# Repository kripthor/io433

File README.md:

# Project IO433

```
 ___ ___  _ _ ________
|_ _/ _ \| | |__ /__ /
 | | (_) |_  _|_ \|_ \
|___\___/  |_|___/___/
                       
```
##
This is a fork (v0.21) for my personal use of the original io433 project by Krypthor.
Added "Jam" capability. This is really fun, no on in vincity can use 433Mhz devices :))

## Description

IO433 is an open-source ESP32 (TTGO T-Display) & CC1101 based 433Mhz sniffer. It is currently work in progress.
It can sniff, store, replay, dump and monitor most 433Mhz (currently ASK-OOK only) signals.
These include garage door openers, remote doorbells, sensors and similar devices.

The core of this project aims to be its simplicity, reliability and versatility.
With a couple of ICs and a by 'connecting some wires', or soldering a breakout board, one can start messing around with 433Mhz devices and decode their communications protocols.
It's mainly a proof-of-concept but already encompasses several very useful features.

```bash
│  # The current dir is a platformIO project and can be imported straight from here.
├── arduino  # an example arduino project that implements a remote for some ASK-OOK-PWM signals based on a FS1000A
├── docs     # docs and pictures
├── include  # project helper files 
├── lib    #some needed libraries with specific modifications for this project
├── libsigrokdecode   # a modified PWM decoder that shows bits and nibbles (sigrok/PulseView)
└── src # project main files
```

## Bill of Materials

| Qty. | Description | Obs. |
|------|------------------------|-----------------------------------------------------------------|
| 1 | ESP32 TTGO T-Display | ESP32 controller with a 1.14" LCD and two buttons for navigation |
| 1 | TI-CC1101 or E07-M1101D | CC1101 based modules for 433Mhz (and other frequencies) communications |
| 1 | io433 PCB| Order a PCB or etch one or just grab some wires :) |
| 1 | Battery | Optional 3.7v battery

* All the components can be easily found in the usual online stores such as *AliExpress* ([ESP32 TTGO T-Display](https://aliexpress.com/wholesale?SearchText=ttgo+t+display+esp32)) - [CC1101](https://aliexpress.com/wholesale?SearchText=cc1101)), *Amazon*, *eBay*, etc.
* The breakout pcb and schematics files are under the docs/ directory: 
[IO433 Schematic](docs/breakout.sch)
[IO433 Board](docs/breakout.brd)

## IO433 Wiring

### Prototype photo and assembly suggestion

This is just a suggestion on how to wire the ESP32 and the CC1101. A perforated PCB can be used to make the prototype more sturdy. Or you can just order a pre-fabricated board, like the one bellow:

### IO433 Wiring

Details of the wiring between the ESP32 and TI-CC1101 (above) and the E07-M1101D (below). The pinout choosing is important. If changed, not only the code should change to reflect the new pinout, as one must make sure the corresponding ports on the ESP32 support the I/O operation mode that the code needs. 
* **Important note**: the green wire connects to IO2 on the ESP32, regardless of what you see in some pictures.
* **Important note 2**: You need to change the file ./include/CC1101utils.h to reflect which CC1101 model you are using.

### IO433 PCB Schematics
docs/breakout.sch

docs/breakout.brd

### Assembly with PCB

Solder the CC1101 based module in the lower leftmost side of the pcb. The E07-M1101D will have 2x4 pins and the TI-CC1101 will have 2x5 pins. If you are using the E07-M1101D, connect the solderable jumper in the lower middle.  

Then just solder the ESP32 TTGO module on the PCB. Add a battery or just use the USB cable to power the module. Optionally print the 3D case for your CC1101 module. 
I've made an Youtube video to show how to assemble it in less than half an hour: [IO433 Assembly on Youtube](https://www.youtube.com/watch?v=Nz-Mw6mhYjg)

### Assembly with battery and 3D printed case, no PCB

If you want, you can use the 3D printed case that supports a 902540 720mAh or even a 903048 1800mAh, 3.7V battery (should last for some days)
The full material is listed bellow:

### 3D case

NO PCB version:
Tinker/download it from [tinkercad](https://www.tinkercad.com/things/bPiFpUXC7pQ)
or grab the STL from the [docs](docs/IO433.stl)

PCB Version:
Tinker/download, both TI-CC1101 and E07-M1101 versions, from  [tinkercad](https://www.tinkercad.com/things/0qDgP6hPqE1)

## How to flash IO433   

### Using [Platformio](https://platformio.org/)

* Install Visual Studio
* Install PlatformIO from the Extensions (restart)
* Install the Espressif 32 platform from the PlatformIO Embedded tab (restart)
* Clone the repository
* Change the file ./include/CC1101utils.h and uncomment your CC1101 version(either the TICC1101 or the E07M1101D)
* Connect USB-C cable to TTGO
* Build and upload

## How to use it

Plug the ESP32 to a battery or a to a USB-C cable. The current menu structure is the following:

```bash
│ Main
├── Copy   # Copy signal to current memory bank
├── Replay # Replay signal from current memory bank
├── Dump   # Dump current memory bank to screen and serial (fixed 100kbps, for easy analysis on third party software [ex. PulseView])
└── More
    ├── Monitor # Dump raw signal to screen and RSSI info
    ├── Jam     # Simple jam / send random bits on radio
    ├── Raw Out # Dump current signal to serial as fast as possible (default 1Mbps serial)
    └── About   # About menu
```

## Button behaviour

* UP and DOWN short press, moves between menu items
* UP long press is moves back a level
* DOWN long press enters current submenu or function
* UP or DOWN double press moves back and forward from memory banks (to store/replay multiple signals) 

## Dependencies

This project uses:

 * Button2 lib (which should auto-update on build via platformio.ini)
 * SmartRC-CC1101-Driver-Lib (on /lib, added minor changes for the ESP32 TDisplay)
 * TFT_eSPI (on /lib, added minor changes for the ESP32 TDisplay)

# Improvements

There are many possibilities for improvements:

* Code refactoring. Make SimpleMenu a proper lib.
* Better SPIFFS management
* Configuration menus for changing output data rates and formats
* Configuration menus for CC1101 setup: frequencies, modulations, data rates and bandwidth
* Implement other modulations besides ASK-OOK
* Add upload data files from PC to be replayed
* Add accept from serial and transmit features
* and so forth...

Feel free to clone and play around, as well as to contribute and make a pull request.

## Kudos

* [LSatan](https://github.com/LSatan), for the SmartRC-CC1101-Driver-Lib
* the [TFT_eSPI Library](https://github.com/Bodmer/TFT_eSPI)
* Shameless README.md 'template' rip from [jpdias](https://github.com/jpdias)

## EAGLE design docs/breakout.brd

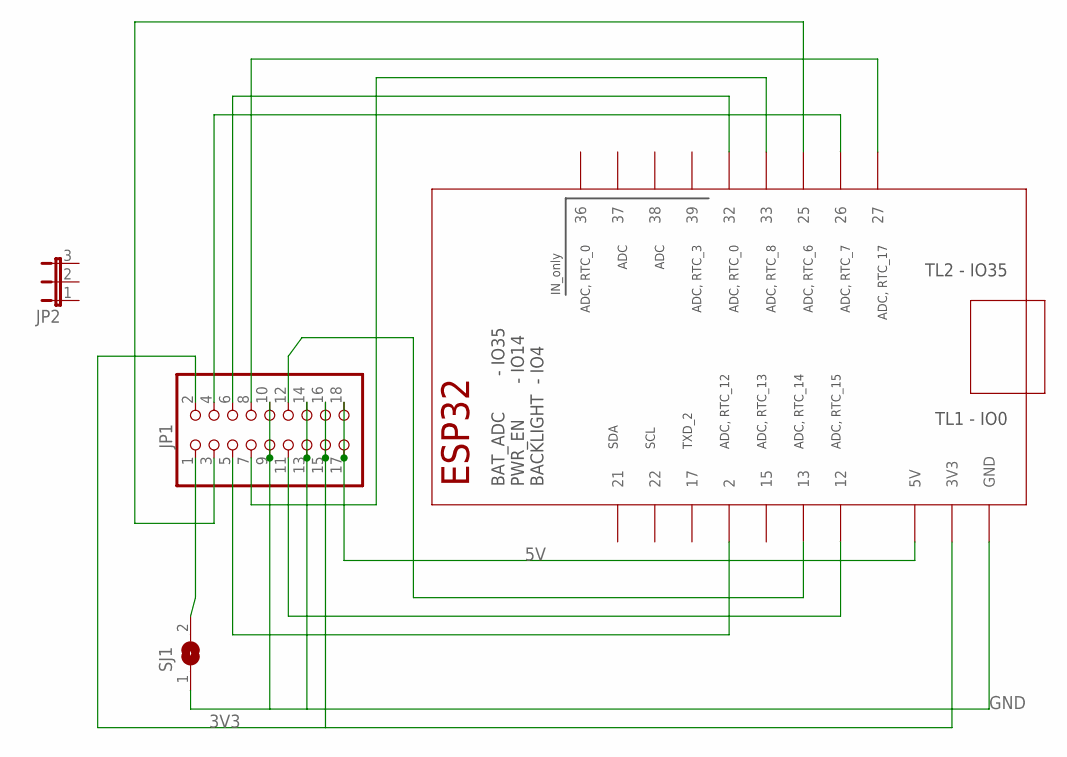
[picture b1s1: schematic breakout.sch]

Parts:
IC1: TTGO_DISP; TTGO_DISP_DEFAULT
JP1: PINHD-2X9-BIG; 2X09-BIG
JP2: JUMPER3
SJ1: SOLDERJUMPERREFLOW; SOLDERJUMPER_REFLOW

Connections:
3V3: IC1.3V3_1 (3V3), IC1.3V3_2 (3V3), JP1.2, JP1.15, JP1.16
5V: IC1.5V, JP1.17, JP1.18
GND: IC1.GND_1 (GND), IC1.GND_2 (GND), IC1.GND_3 (GND), IC1.GND_4 (GND), IC1.GND_5 (GND), JP1.9, JP1.10, JP1.13, JP1.14, SJ1.1
unnamed: IC1.13, JP1.12
unnamed: JP1.1, SJ1.2
unnamed: IC1.27, JP1.8
unnamed: IC1.33, JP1.7
unnamed: IC1.32, JP1.6
unnamed: IC1.26, JP1.4
unnamed: IC1.2, JP1.5
unnamed: IC1.25, JP1.3
unnamed: IC1.12, JP1.11

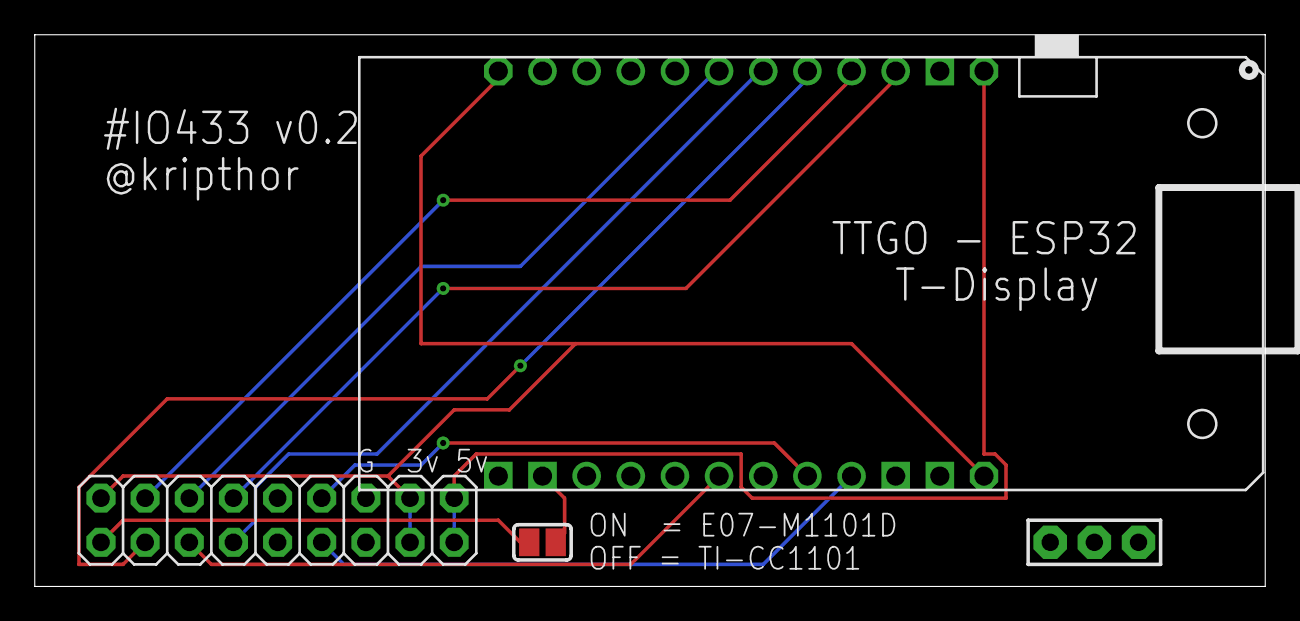
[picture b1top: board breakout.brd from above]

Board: 2 copper layers, 70.8 x 31.7 mm, 4 parts (0 on the bottom side), 12 nets.

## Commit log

2021-04-12 Quick hack to support multiple signals
2021-04-12 Added comments
2021-04-12 Added basic SPIFFS
2021-04-13 Minor changes
2021-04-21 Added README.md
2021-04-21 Updated pictures
2021-04-21 Update pictures
2021-04-21 Changed logo
2021-04-21 V0.1
2021-04-22 Fixed typos
2021-04-26 Example arduino code
2021-04-27 Added sigrok PWM filter. Added comments.
2021-04-27 Re-organized libs
2021-04-27 Added some notes
2021-04-29 Added deep sleep on idle for battery devices. V0.2
2021-05-04 Added links to buy the hardware
2021-05-04 Added links to buy on AliExpress
2021-06-15 3D case and pics
2021-06-15 Fixed assembly2 link
2021-06-15 Full assembly pic
2021-06-15 link to stl
2021-07-05 dont drop first value of signal when saving to spiffs
    as `i` was incremented in the `while` statement, the loop would start
    with `i == 1` and thus not saving the first element of `signal433_store`
    to the flash.
2021-07-05 Improved deep sleep to around 9mA
2022-11-03 new version starts
2022-11-10 v0.2
2022-11-14 CC1101utils had the defines switched for TI-CC1101 and the E07-M1101D
2022-11-14 New wiring
2022-11-14 Youtube link added
2022-11-14 Fixed some links
2022-11-14 Fixed links
2022-11-15 FIxed version and broken build
2022-11-28 Fix "cannot open source file "esp_deep_sleep.h"
    esp_deep_sleep.h was deprecated in IDF in favor of esp_sleep.h which has already been updated in Arduino
2022-11-28 Updated esp_deep_sleep to esp_sleep, minor code changes. Please update your platformio Espressif libraries to the latest version if you have problems compiling.
2024-03-02 first commit for jam capability
2024-03-02 commit for jam capability

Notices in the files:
parts and their libraries:
microbuilder: This work is placed in the public domain, and may be freely used for commercial and non-commercial work with the following conditions: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
